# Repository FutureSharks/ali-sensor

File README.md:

# ali-sensor

A multi-sensor device for [Home Assistant](https://www.home-assistant.io/) built around cheap parts from [AliExpress](https://aliexpress.com/). This project is essentially a [PCB design](pcb) and [ESPHome](https://esphome.io/) configuration that allows you to build a customisable device that could detect presence and measure light, CO₂, temperature, humidity, VOCs and more. You can choose a selection of sensors available from your favourite marketplace of questionable but cheap goods.

The PCB is designed around an [ESP32-C6 Super Mini](https://www.espboards.dev/esp32/esp32-c6-super-mini/) and features:

- Space for a single [HLK-LD2410C](https://www.hlktech.net/index.php?id=1095) Human Presence sensor
- 2x I2C sensor stacks where many different sensors can be connected
- 4x GPIO out
- I2C bus power selector for 3.3V or 5V
- Power connector or alternatively use the USB-C connector from the ESP32-C6

## Example build

This example build measures Lux, CO₂ , VOCs, NOx index, temperature, humidity, presence and motion using the following devices from AliExpress:

- ESP32-C6 Super Mini (4.90€)
- HLK-LD2410C Human Presence & Distance Detection Radar Sensor Module (3.70€)
- SGP41 VOC and NOx sensor (12€)
- SCD41 CO₂ sensor (23€)
- VEML7700 High accuracy ambient light sensor (3.85€)

Total cost is about 47€, very reasonable given that it includes high quality gas and CO₂ sensors.

## The sensors

There are a number of suitable sensors from not just AliExpress but also [Adafruit](https://www.adafruit.com/) (actually I think they created the layout/footprint of these sensors). Look for the sensors that have this 5 pin and mounting hole layout:

Some examples I have found:

- SGP41 VOC and NOx sensor (AliExpress)
- SCD41 CO₂ sensor (AliExpress)
- VEML7700 light sensor (AliExpress)
- SGP30 indoor air quality gas sensor (AliExpress)
- SHT45 Precision Temp & Humidity (Adafruit)
- Si7021 Temperature & Humidity Sensor (Adafruit)
- SHTC3 Temperature & Humidity (Adafruit)
- QMC5883P Triple axis agnetometer (Adafruit)
- MMC5603 Triple axis agnetometer (Adafruit)
- TLV493D Triple-Axis Magnetometer (Adafruit)
- MS8607 Pressure Humidity Temperature (Adafruit)

Some photos of these sensors are collected in [img/sensors](img/sensors) to make finding the correct version on AliExpress easier.

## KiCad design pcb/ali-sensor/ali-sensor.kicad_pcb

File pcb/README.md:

# PCB and schematic

The PCB and schematic are made with [KiCad](https://www.kicad.org/). The project files are in [ali-sensor](ali-sensor)

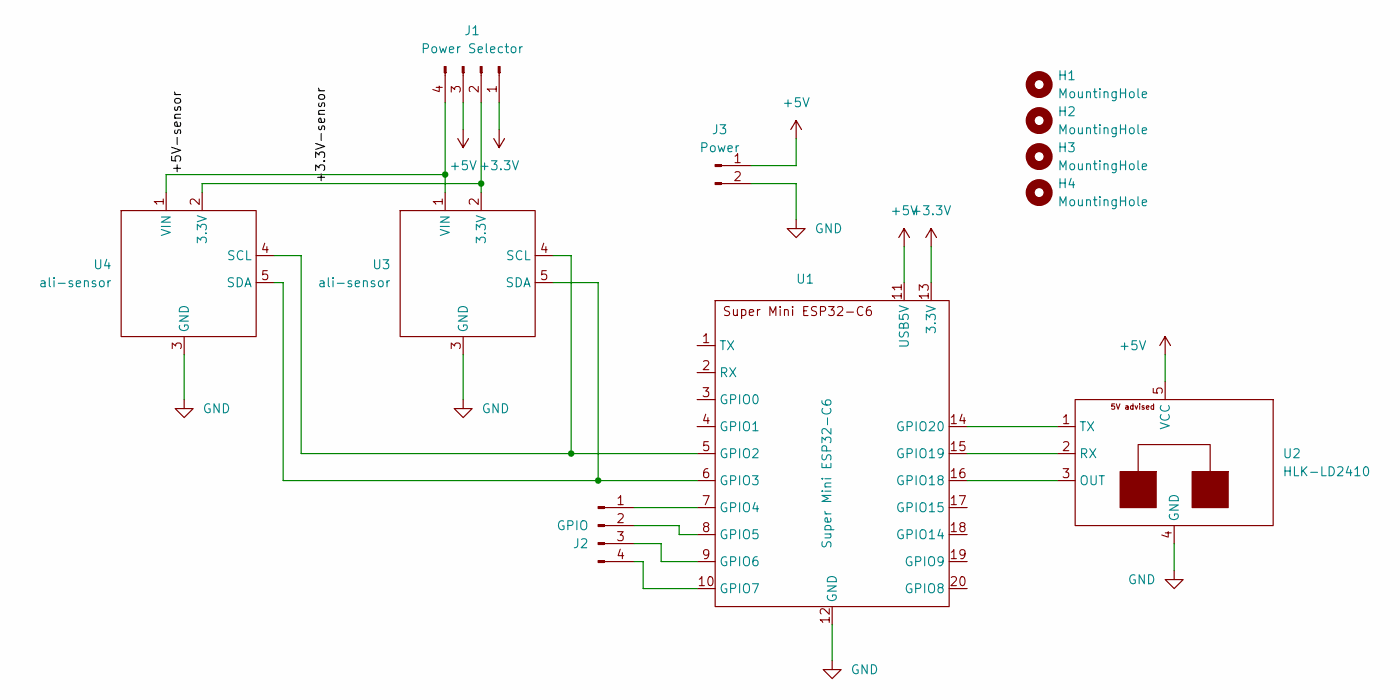
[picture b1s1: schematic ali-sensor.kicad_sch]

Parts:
H1, H2, H3, H4: MountingHole; MountingHole_3.2mm_M3
J1: Power Selector; PinHeader_1x04_P2.54mm_Vertical
J2: GPIO; Molex_KK-254_AE-6410-04A_1x04_P2.54mm_Vertical
J3: Power; Molex_KK-254_AE-6410-02A_1x02_P2.54mm_Vertical
U1: Super Mini ESP32-C6; ESP32-C6
U2: HLK-LD2410; HLK-LD2410C
U3, U4: ali-sensor

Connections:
+3.3V: J1.1, U1.13 (3.3V)
+5V: J1.3, J3.1, U1.11 (USB5V), U2.5 (VCC)
/+3.3V-sensor: J1.2, U3.2 (3.3V), U4.2 (3.3V)
/+5V-sensor: J1.4, U3.1 (VIN), U4.1 (VIN)
GND: J3.2, U1.12 (GND), U2.4 (GND), U3.3 (GND), U4.3 (GND)
unnamed: J2.1, U1.7 (GPIO4)
unnamed: J2.2, U1.8 (GPIO5)
unnamed: J2.3, U1.9 (GPIO6)
unnamed: J2.4, U1.10 (GPIO7)
unnamed: U1.5 (GPIO2), U3.4 (SCL), U4.4 (SCL)
unnamed: U1.6 (GPIO3), U3.5 (SDA), U4.5 (SDA)
unnamed: U1.16 (GPIO18), U2.3 (OUT)
unnamed: U1.15 (GPIO19), U2.2 (RX)
unnamed: U1.14 (GPIO20), U2.1 (TX)

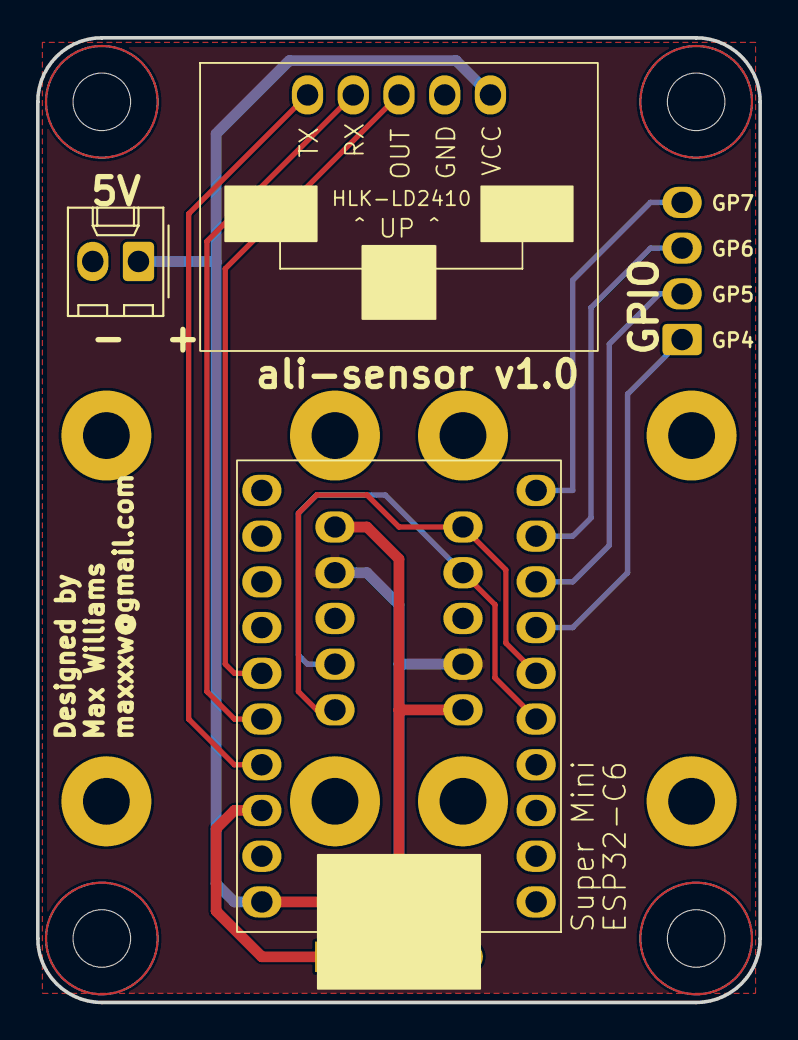
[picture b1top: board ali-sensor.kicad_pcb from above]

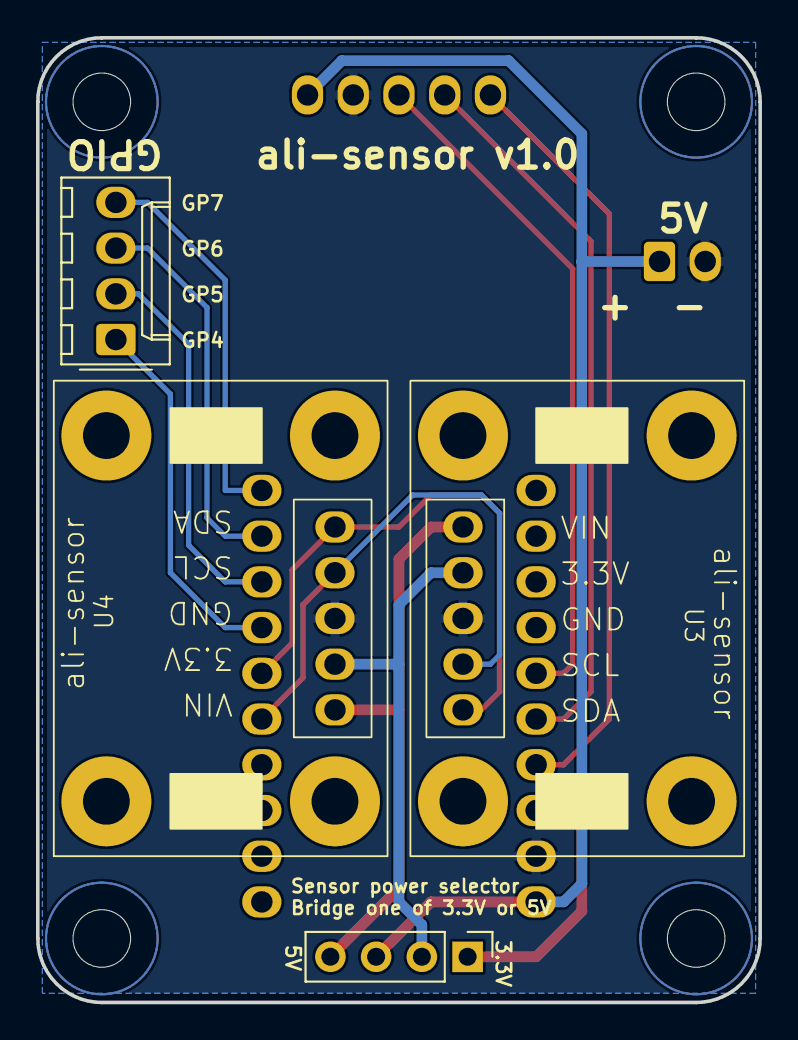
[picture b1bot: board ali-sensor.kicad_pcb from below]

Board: 2 copper layers, 40.1 x 53.6 mm, 11 parts (4 on the bottom side), 14 nets.

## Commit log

2025-10-26 add more images
